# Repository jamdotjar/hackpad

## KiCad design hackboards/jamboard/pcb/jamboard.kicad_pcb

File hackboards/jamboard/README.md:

# Jamboard

BOM:
- 1x PCB
- 3d printed case
- 2x Orpheus Pico

https://chosfox.com/products/outemu-silent-honey-peach-switch?variant=44545283260610

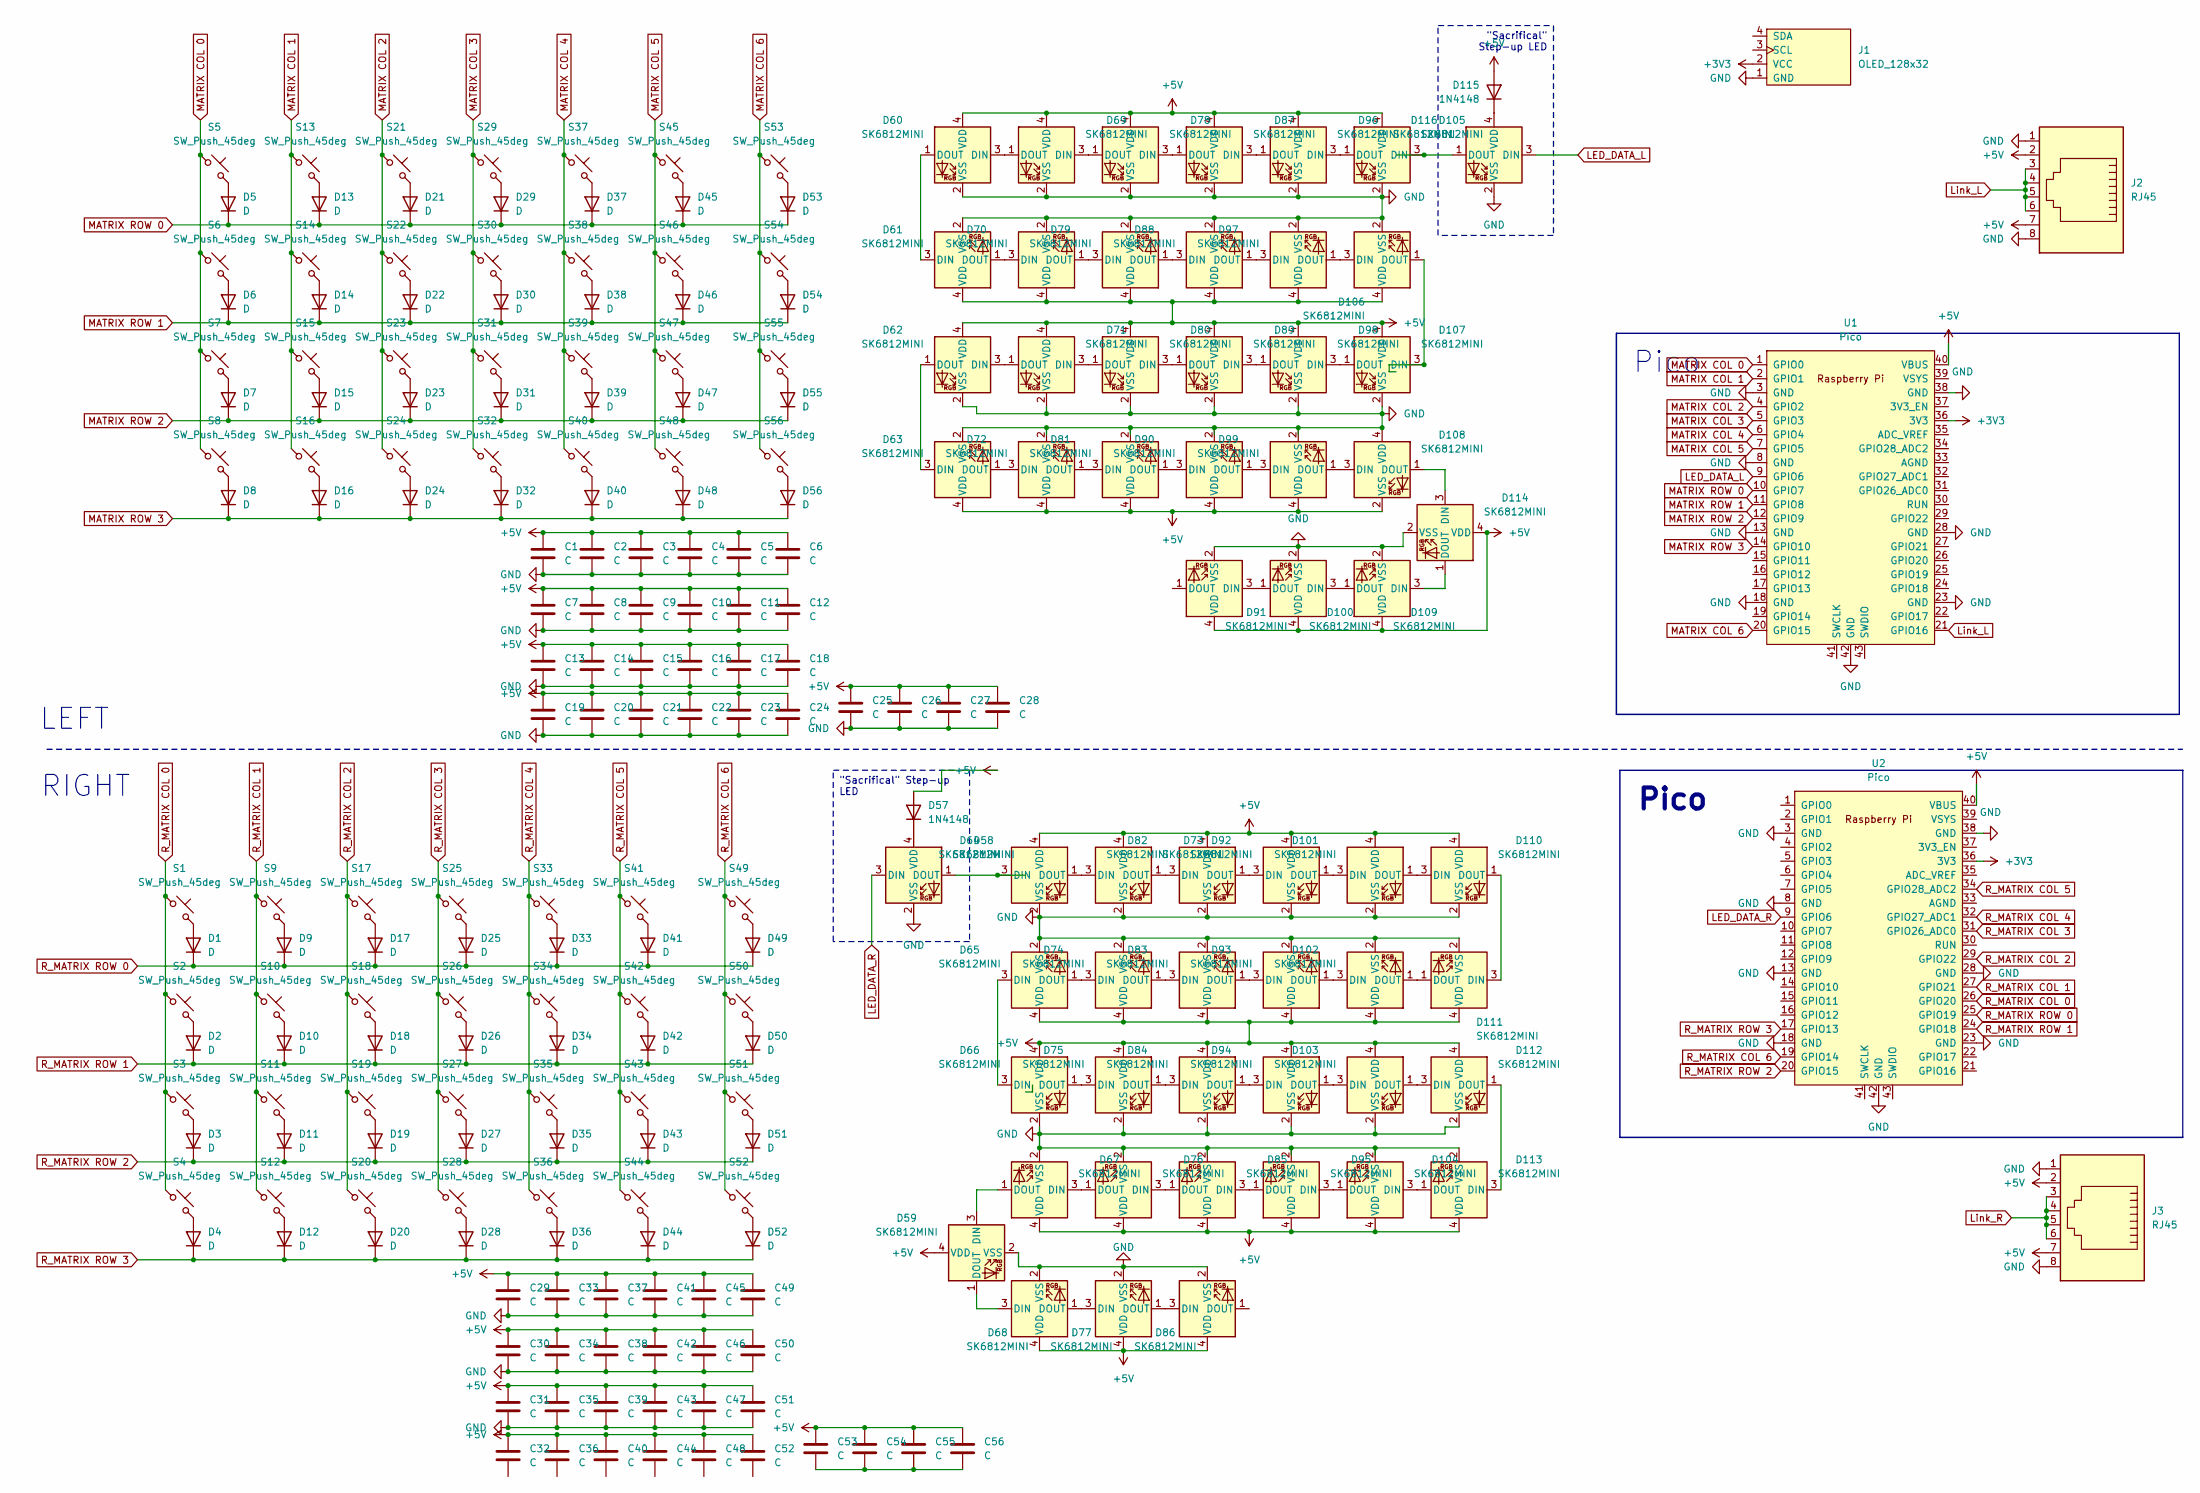
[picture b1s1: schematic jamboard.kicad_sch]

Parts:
C1, C2, C3, C4, C5, C6, C7, C8, C9, C10, C11, C12, C13, C14, C15, C16, C17, C18, C19, C20, C21, C22, C23, C24, C25, C26, C27, C28, C29, C30, C31, C32, C33, C34, C35, C36, C37, C38, C39, C40, C41, C42, C43, C44, C45, C46, C47, C48, C49, C50, C51, C52, C53, C54, C55, C56: C; C_0603_1608Metric_Pad1.08x0.95mm_HandSolder
D1, D2, D3, D4, D5, D6, D7, D8, D9, D10, D11, D12, D13, D14, D15, D16, D17, D18, D19, D20, D21, D22, D23, D24, D25, D26, D27, D28, D29, D30, D31, D32, D33, D34, D35, D36, D37, D38, D39, D40, D41, D42, D43, D44, D45, D46, D47, D48, D49, D50, D51, D52, D53, D54, D55, D56: D; Diode
D57, D115: 1N4148; D_DO-35_SOD27_P7.62mm_Horizontal
D58, D59, D60, D61, D62, D63, D64, D65, D66, D67, D68, D69, D70, D71, D72, D73, D74, D75, D76, D77, D78, D79, D80, D81, D82, D83, D84, D85, D86, D87, D88, D89, D90, D91, D92, D93, D94, D95, D96, D97, D98, D99, D100, D101, D102, D103, D104, D105, D106, D107, D108, D109, D110, D111, D112, D113, D114, D116: SK6812MINI; SK6812MINI-E
J1: OLED_128x32; SSD1306-0.91-OLED-4pin-128x32
J2, J3: RJ45; RJ45_Amphenol_54602-x08_Horizontal
S1, S2, S3, S4, S5, S6, S7, S8, S9, S10, S11, S12, S13, S14, S15, S16, S17, S18, S19, S20, S21, S22, S23, S24, S25, S26, S27, S28, S29, S30, S31, S32, S33, S34, S35, S36, S37, S38, S39, S40, S41, S42, S43, S44, S45, S46, S47, S48, S49, S50, S51, S52, S53, S54, S55, S56: SW_Push_45deg; MX-Hotswap-1U
U1, U2: Pico; RaspberryPi_Pico_Common

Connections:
+3V3: J1.2 (VCC), U1.36 (3V3), U2.36 (3V3)
+5V: C1.1, C2.1, C3.1, C4.1, C5.1, C6.1, C7.1, C8.1, C9.1, C10.1, C11.1, C12.1, C13.1, C14.1, C15.1, C16.1, C17.1, C18.1, C19.1, C20.1, C21.1, C22.1, C23.1, C24.1, C25.1, C26.1, C27.1, C28.1, C29.1, C30.1, C31.1, C32.1, C33.1, C34.1, C35.1, C36.1, C37.1, C38.1, C39.1, C40.1, C41.1, C42.1, C43.1, C44.1, C45.1, C46.1, C47.1, C48.1, C49.1, C50.1, C51.1, C52.1, C53.1, C54.1, C55.1, C56.1, D57.2 (A), D59.4 (VDD), D60.4 (VDD), D61.4 (VDD), D62.4 (VDD), D63.4 (VDD), D64.4 (VDD), D65.4 (VDD), D66.4 (VDD), D67.4 (VDD), D68.4 (VDD), D69.4 (VDD), D70.4 (VDD), D71.4 (VDD), D72.4 (VDD), D73.4 (VDD), D74.4 (VDD), D75.4 (VDD), D76.4 (VDD), D77.4 (VDD), D78.4 (VDD), D79.4 (VDD), D80.4 (VDD), D81.4 (VDD), D82.4 (VDD), D83.4 (VDD), D84.4 (VDD), D85.4 (VDD), D86.4 (VDD), D87.4 (VDD), D88.4 (VDD), D89.4 (VDD), D90.4 (VDD), D91.4 (VDD), D92.4 (VDD), D93.4 (VDD), D94.4 (VDD), D95.4 (VDD), D96.4 (VDD), D97.4 (VDD), D98.4 (VDD), D99.4 (VDD), D100.4 (VDD), D101.4 (VDD), D102.4 (VDD), D103.4 (VDD), D104.4 (VDD), D105.4 (VDD), D106.4 (VDD), D107.4 (VDD), D108.2 (VSS), D109.4 (VDD), D110.4 (VDD), D111.4 (VDD), D112.4 (VDD), D113.4 (VDD), D114.4 (VDD), D115.2 (A), J2.2, J2.7, J3.2, J3.7, U1.40 (VBUS), U2.40 (VBUS)
GND: C1.2, C2.2, C3.2, C4.2, C5.2, C6.2, C7.2, C8.2, C9.2, C10.2, C11.2, C12.2, C13.2, C14.2, C15.2, C16.2, C17.2, C18.2, C19.2, C20.2, C21.2, C22.2, C23.2, C24.2, C25.2, C26.2, C27.2, C28.2, C29.2, C30.2, C31.2, C33.2, C34.2, C35.2, C37.2, C38.2, C39.2, C41.2, C42.2, C43.2, C45.2, C46.2, C47.2, C49.2, C50.2, C51.2, D58.2 (VSS), D59.2 (VSS), D60.2 (VSS), D61.2 (VSS), D62.2 (VSS), D63.2 (VSS), D64.2 (VSS), D65.2 (VSS), D66.2 (VSS), D67.2 (VSS), D68.2 (VSS), D69.2 (VSS), D70.2 (VSS), D71.2 (VSS), D72.2 (VSS), D73.2 (VSS), D74.2 (VSS), D75.2 (VSS), D76.2 (VSS), D77.2 (VSS), D78.2 (VSS), D79.2 (VSS), D80.2 (VSS), D81.2 (VSS), D82.2 (VSS), D83.2 (VSS), D84.2 (VSS), D85.2 (VSS), D86.2 (VSS), D87.2 (VSS), D88.2 (VSS), D89.2 (VSS), D90.2 (VSS), D91.2 (VSS), D92.2 (VSS), D93.2 (VSS), D94.2 (VSS), D95.2 (VSS), D96.2 (VSS), D97.2 (VSS), D98.2 (VSS), D99.2 (VSS), D100.2 (VSS), D101.2 (VSS), D102.2 (VSS), D103.2 (VSS), D104.2 (VSS), D105.2 (VSS), D106.2 (VSS), D107.2 (VSS), D108.4 (VDD), D109.2 (VSS), D110.2 (VSS), D111.2 (VSS), D112.2 (VSS), D113.2 (VSS), D114.2 (VSS), D116.2 (VSS), J1.1 (GND), J2.1, J2.8, J3.1, J3.8, U1.3 (GND), U1.8 (GND), U1.13 (GND), U1.18 (GND), U1.23 (GND), U1.28 (GND), U1.38 (GND), U1.42 (GND), U2.3 (GND), U2.8 (GND), U2.13 (GND), U2.18 (GND), U2.23 (GND), U2.28 (GND), U2.38 (GND), U2.42 (GND)
LED_DATA_L: D116.3 (DIN), U1.9 (GPIO6)
LED_DATA_R: D58.3 (DIN), U2.9 (GPIO6)
Link_L: J2.3, J2.4, J2.5, J2.6, U1.21 (GPIO16)
Link_R: J3.3, J3.4, J3.5, J3.6
MATRIX COL 0: S5.1, S6.1, S7.1, S8.1, U1.1 (GPIO0)
MATRIX COL 1: S13.1, S14.1, S15.1, S16.1, U1.2 (GPIO1)
MATRIX COL 2: S21.1, S22.1, S23.1, S24.1, U1.4 (GPIO2)
MATRIX COL 3: S29.1, S30.1, S31.1, S32.1, U1.5 (GPIO3)
MATRIX COL 4: S37.1, S38.1, S39.1, S40.1, U1.6 (GPIO4)
MATRIX COL 5: S45.1, S46.1, S47.1, S48.1, U1.7 (GPIO5)
MATRIX COL 6: S53.1, S54.1, S55.1, S56.1, U1.20 (GPIO15)
MATRIX ROW 0: D5.1 (K), D13.1 (K), D21.1 (K), D29.1 (K), D37.1 (K), D45.1 (K), D53.1 (K), U1.10 (GPIO7)
MATRIX ROW 1: D6.1 (K), D14.1 (K), D22.1 (K), D30.1 (K), D38.1 (K), D46.1 (K), D54.1 (K), U1.11 (GPIO8)
MATRIX ROW 2: D7.1 (K), D15.1 (K), D23.1 (K), D31.1 (K), D39.1 (K), D47.1 (K), D55.1 (K), U1.12 (GPIO9)
MATRIX ROW 3: D8.1 (K), D16.1 (K), D24.1 (K), D32.1 (K), D40.1 (K), D48.1 (K), D56.1 (K), U1.14 (GPIO10)
unnamed: C53.2, C54.2, C55.2, C56.2
unnamed: D1.2 (A), S1.2
unnamed: D2.2 (A), S2.2
unnamed: D3.2 (A), S3.2
unnamed: D4.2 (A), S4.2
unnamed: D5.2 (A), S5.2
unnamed: D6.2 (A), S6.2
unnamed: D7.2 (A), S7.2
unnamed: D8.2 (A), S8.2
unnamed: D9.2 (A), S9.2
unnamed: D10.2 (A), S10.2
unnamed: D11.2 (A), S11.2
unnamed: D12.2 (A), S12.2
unnamed: D13.2 (A), S13.2
unnamed: D14.2 (A), S14.2
unnamed: D15.2 (A), S15.2
unnamed: D16.2 (A), S16.2
unnamed: D17.2 (A), S17.2
unnamed: D18.2 (A), S18.2
unnamed: D19.2 (A), S19.2
unnamed: D20.2 (A), S20.2
unnamed: D21.2 (A), S21.2
unnamed: D22.2 (A), S22.2
unnamed: D23.2 (A), S23.2
unnamed: D24.2 (A), S24.2
unnamed: D25.2 (A), S25.2
unnamed: D26.2 (A), S26.2
unnamed: D27.2 (A), S27.2
unnamed: D28.2 (A), S28.2
unnamed: D29.2 (A), S29.2
unnamed: D30.2 (A), S30.2
unnamed: D31.2 (A), S31.2
unnamed: D32.2 (A), S32.2
unnamed: D33.2 (A), S33.2
unnamed: D34.2 (A), S34.2
unnamed: D35.2 (A), S35.2
unnamed: D36.2 (A), S36.2
unnamed: D37.2 (A), S37.2
unnamed: D38.2 (A), S38.2
unnamed: D39.2 (A), S39.2
unnamed: D40.2 (A), S40.2
unnamed: D41.2 (A), S41.2
unnamed: D42.2 (A), S42.2
unnamed: D43.2 (A), S43.2
unnamed: D44.2 (A), S44.2
unnamed: D45.2 (A), S45.2
unnamed: D46.2 (A), S46.2
unnamed: D47.2 (A), S47.2
unnamed: D48.2 (A), S48.2
unnamed: D49.2 (A), S49.2
unnamed: D50.2 (A), S50.2
unnamed: D51.2 (A), S51.2
unnamed: D52.2 (A), S52.2
unnamed: D53.2 (A), S53.2
unnamed: D54.2 (A), S54.2
unnamed: D55.2 (A), S55.2
unnamed: D56.2 (A), S56.2
unnamed: D57.1 (K), D58.4 (VDD)
unnamed: D58.1 (DOUT), D64.3 (DIN)
unnamed: D59.3 (DIN), D67.1 (DOUT)
unnamed: D59.1 (DOUT), D68.3 (DIN)
unnamed: D60.3 (DIN), D69.1 (DOUT)
unnamed: D60.1 (DOUT), D61.3 (DIN)
unnamed: D61.1 (DOUT), D70.3 (DIN)
unnamed: D62.3 (DIN), D71.1 (DOUT)
unnamed: D62.1 (DOUT), D63.3 (DIN)
unnamed: D63.1 (DOUT), D72.3 (DIN)
unnamed: D64.1 (DOUT), D73.3 (DIN)
unnamed: D65.3 (DIN), D66.3 (DIN)
unnamed: D65.1 (DOUT), D74.3 (DIN)
unnamed: D66.1 (DOUT), D75.3 (DIN)
unnamed: D67.3 (DIN), D76.1 (DOUT)
unnamed: D68.1 (DOUT), D77.3 (DIN)
unnamed: D69.3 (DIN), D78.1 (DOUT)
unnamed: D70.1 (DOUT), D79.3 (DIN)
unnamed: D71.3 (DIN), D80.1 (DOUT)
unnamed: D72.1 (DOUT), D81.3 (DIN)
unnamed: D73.1 (DOUT), D82.3 (DIN)
unnamed: D74.1 (DOUT), D83.3 (DIN)
unnamed: D75.1 (DOUT), D84.3 (DIN)
unnamed: D76.3 (DIN), D85.1 (DOUT)
unnamed: D77.1 (DOUT), D86.3 (DIN)
unnamed: D78.3 (DIN), D87.1 (DOUT)
unnamed: D79.1 (DOUT), D88.3 (DIN)
unnamed: D80.3 (DIN), D89.1 (DOUT)
unnamed: D81.1 (DOUT), D90.3 (DIN)
unnamed: D82.1 (DOUT), D92.3 (DIN)
unnamed: D83.1 (DOUT), D93.3 (DIN)
unnamed: D84.1 (DOUT), D94.3 (DIN)
unnamed: D85.3 (DIN), D95.1 (DOUT)
unnamed: D87.3 (DIN), D96.1 (DOUT)
unnamed: D88.1 (DOUT), D97.3 (DIN)
unnamed: D89.3 (DIN), D98.1 (DOUT)
unnamed: D90.1 (DOUT), D99.3 (DIN)
unnamed: D100.3 (DIN), D109.1 (DOUT)
unnamed: D91.3 (DIN), D100.1 (DOUT)
unnamed: D92.1 (DOUT), D101.3 (DIN)
unnamed: D101.1 (DOUT), D110.3 (DIN)
unnamed: D93.1 (DOUT), D102.3 (DIN)
unnamed: D102.1 (DOUT), D111.1 (DOUT)
unnamed: D94.1 (DOUT), D103.3 (DIN)
unnamed: D103.1 (DOUT), D112.3 (DIN)
unnamed: D104.3 (DIN), D113.1 (DOUT)
unnamed: D95.3 (DIN), D104.1 (DOUT)
unnamed: D105.3 (DIN), D116.1 (DOUT)
unnamed: D96.3 (DIN), D105.1 (DOUT)
unnamed: D97.1 (DOUT), D106.3 (DIN)
unnamed: D106.1 (DOUT), D107.3 (DIN)
unnamed: D98.3 (DIN), D107.1 (DOUT)
unnamed: D99.1 (DOUT), D108.3 (DIN)
unnamed: D108.1 (DOUT), D114.3 (DIN)
unnamed: D109.3 (DIN), D114.1 (DOUT)
unnamed: D110.1 (DOUT), D111.3 (DIN)
unnamed: D112.1 (DOUT), D113.3 (DIN)
unnamed: D115.1 (K), D116.4 (VDD)
R_MATRIX COL 0: S1.1, S2.1, S3.1, S4.1, U2.26 (GPIO20)
R_MATRIX COL 1: S9.1, S10.1, S11.1, S12.1, U2.27 (GPIO21)
R_MATRIX COL 2: S17.1, S18.1, S19.1, S20.1, U2.29 (GPIO22)
R_MATRIX COL 3: S25.1, S26.1, S27.1, S28.1, U2.31 (GPIO26_ADC0)
R_MATRIX COL 4: S33.1, S34.1, S35.1, S36.1, U2.32 (GPIO27_ADC1)
R_MATRIX COL 5: S41.1, S42.1, S43.1, S44.1, U2.34 (GPIO28_ADC2)
R_MATRIX COL 6: S49.1, S50.1, S51.1, S52.1, U2.19 (GPIO14)
R_MATRIX ROW 0: D1.1 (K), D9.1 (K), D17.1 (K), D25.1 (K), D33.1 (K), D41.1 (K), D49.1 (K), U2.25 (GPIO19)
R_MATRIX ROW 1: D2.1 (K), D10.1 (K), D18.1 (K), D26.1 (K), D34.1 (K), D42.1 (K), D50.1 (K), U2.24 (GPIO18)
R_MATRIX ROW 2: D3.1 (K), D11.1 (K), D19.1 (K), D27.1 (K), D35.1 (K), D43.1 (K), D51.1 (K), U2.20 (GPIO15)
R_MATRIX ROW 3: D4.1 (K), D12.1 (K), D20.1 (K), D28.1 (K), D36.1 (K), D44.1 (K), D52.1 (K), U2.17 (GPIO13)

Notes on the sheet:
"Sacrifical" Step-up LED
Pico
RIGHT
LEFT

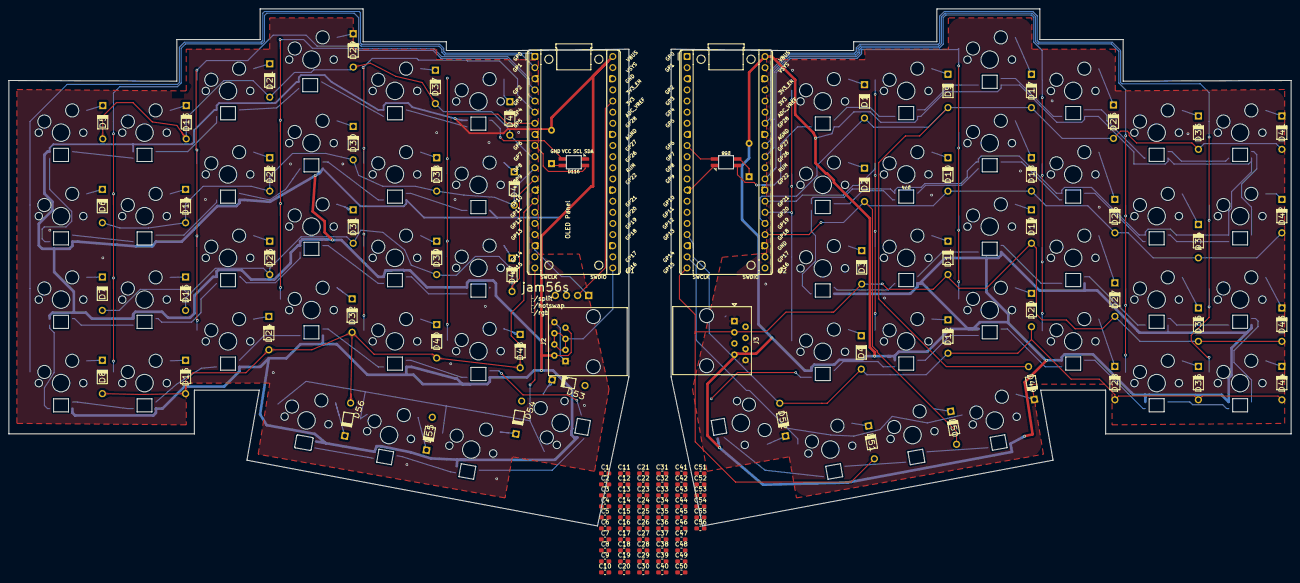
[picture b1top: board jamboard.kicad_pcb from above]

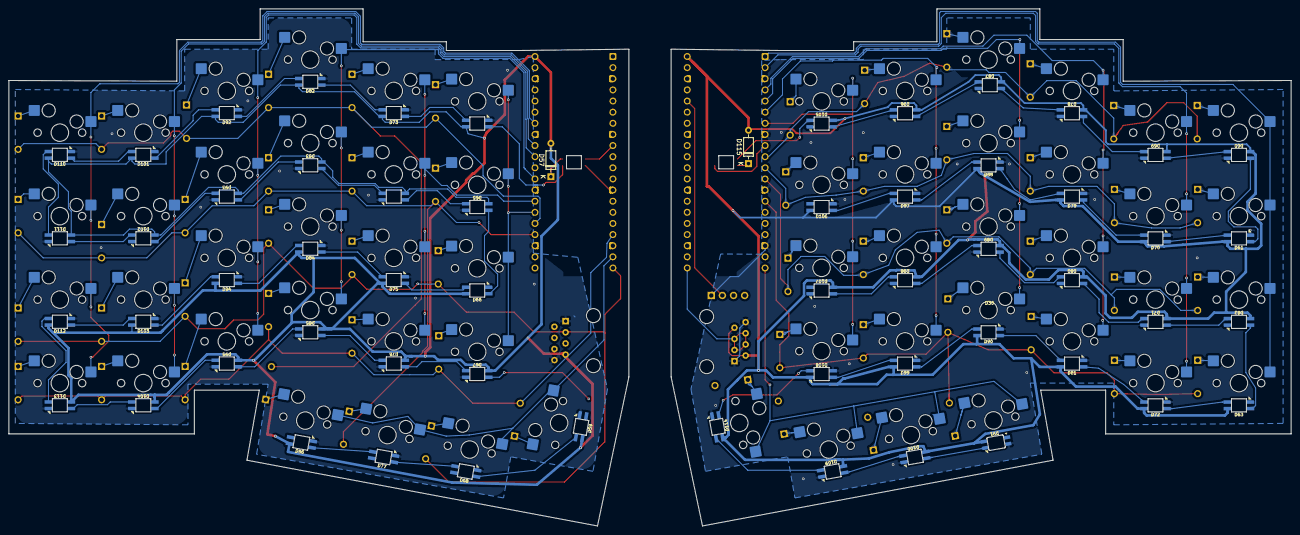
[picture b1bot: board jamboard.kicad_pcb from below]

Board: 2 copper layers, 292.6 x 118.0 mm, 233 parts (114 on the bottom side), 144 nets.

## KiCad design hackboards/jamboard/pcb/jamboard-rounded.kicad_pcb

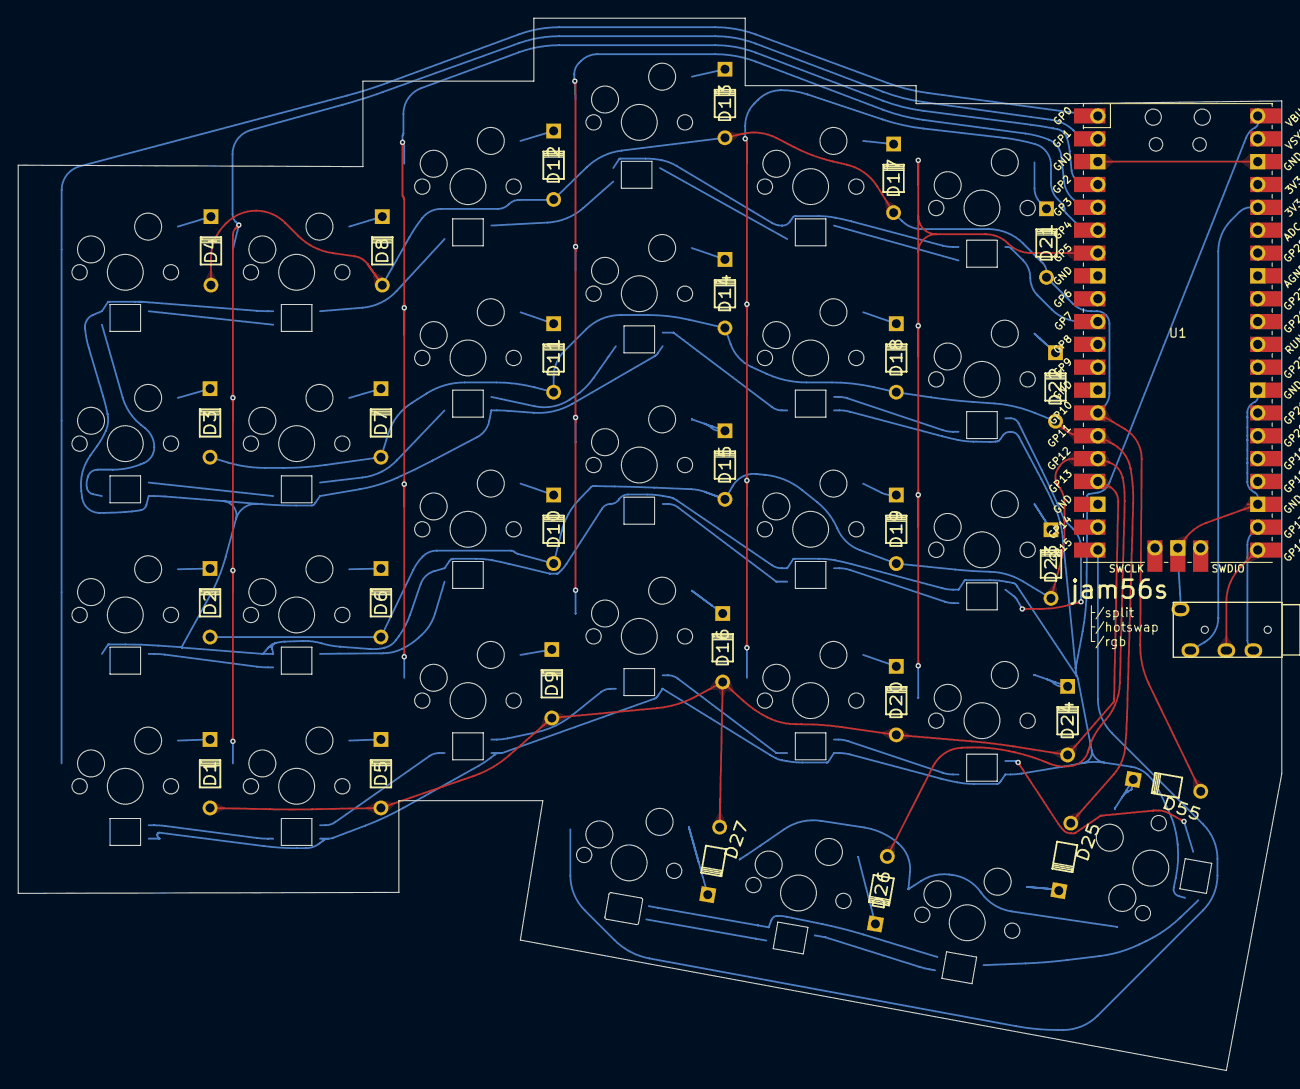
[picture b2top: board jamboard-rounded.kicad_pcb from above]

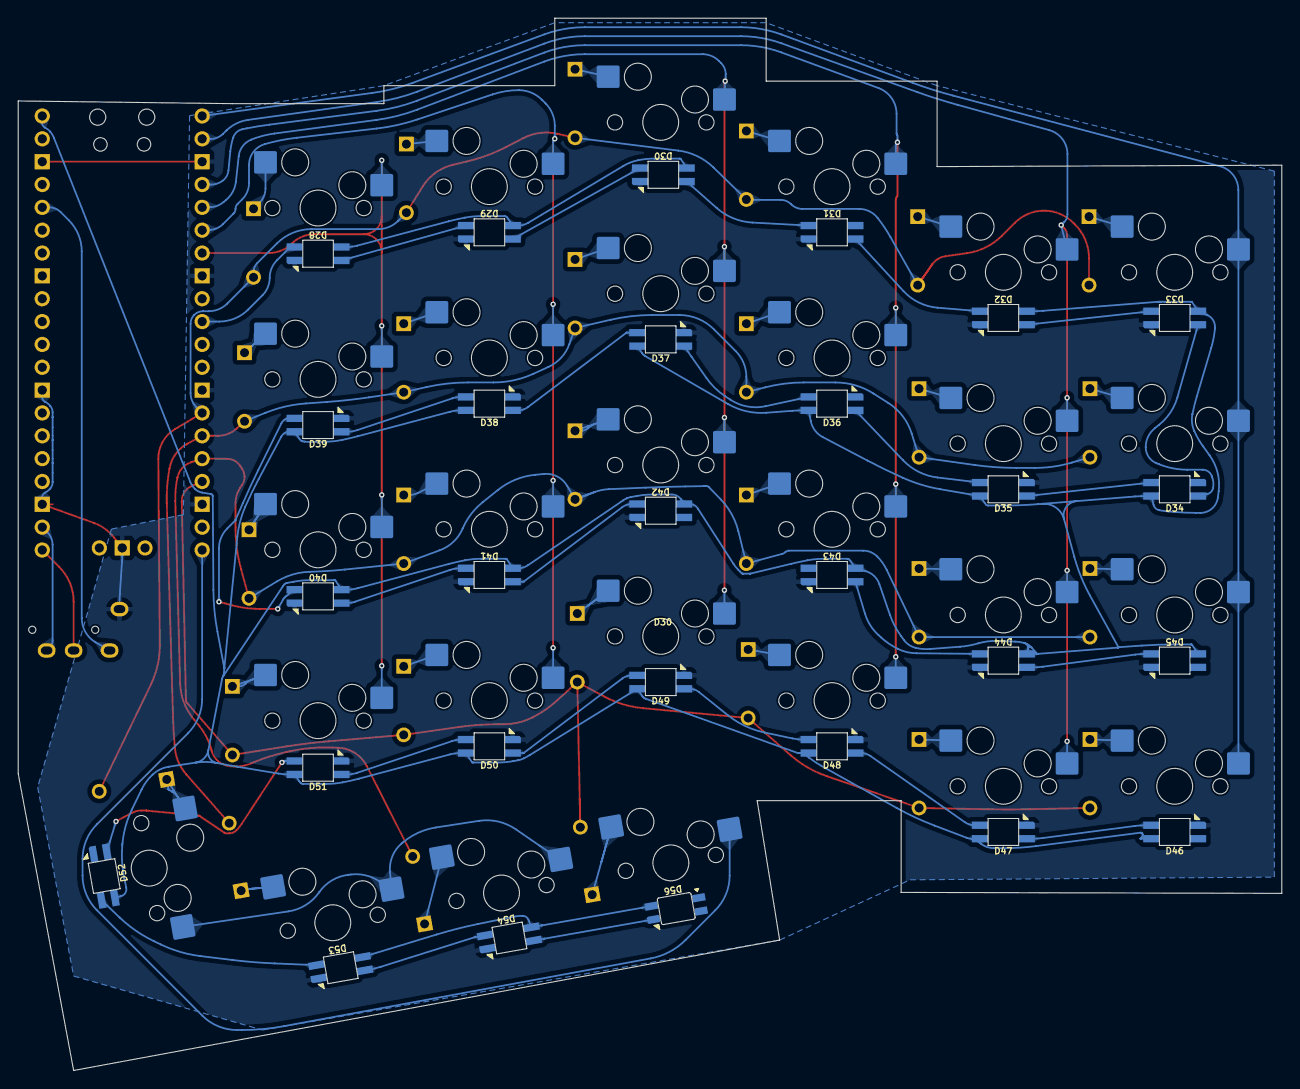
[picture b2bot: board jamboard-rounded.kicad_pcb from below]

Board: 2 copper layers, 140.5 x 117.0 mm, 86 parts (56 on the bottom side), 72 nets.

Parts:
D1, D2, D3, D4, D5, D6, D7, D8, D9, D10, D11, D12, D13, D14, D15, D16, D17, D18, D19, D20, D21, D22, D23, D24, D25, D26, D27, D55: D; Diode
D28, D29, D30, D31, D32, D33, D34, D35, D36, D37, D38, D39, D40, D41, D42, D43, D44, D45, D46, D47, D48, D49, D50, D51, D52, D53, D54: SK6812MINI; SK6812MINI-E
D56: SK6812MINI; SK6812-MINI-E
S1, S2, S3, S4, S5, S6, S7, S8, S9, S10, S11, S12, S13, S14, S15, S16, S17, S18, S19, S20, S21, S22, S23, S24, S25, S26, S27, S28: SW_Push_45deg; MX-Hotswap-1U
U1: Pico; RPi_Pico_SMD_TH
U2: TRRS; TRRS-PJ-320A

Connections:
+3V3: U1.36 (3V3), U2.2 (TIP)
+5V: D28.4 (VDD), D29.4 (VDD), D30.4 (VDD), D31.4 (VDD), D32.4 (VDD), D33.4 (VDD), D34.4 (VDD), D35.4 (VDD), D36.4 (VDD), D37.4 (VDD), D38.4 (VDD), D39.4 (VDD), D40.4 (VDD), D41.4 (VDD), D42.4 (VDD), D43.4 (VDD), D44.4 (VDD), D45.4 (VDD), D46.4 (VDD), D47.4 (VDD), D48.4 (VDD), D49.4 (VDD), D50.4 (VDD), D51.4 (VDD), D52.4 (VDD), D53.4 (VDD), D54.4 (VDD), D56.4 (VDD), U1.40 (VBUS)
GND: D28.2 (VSS), D29.2 (VSS), D30.2 (VSS), D31.2 (VSS), D32.2 (VSS), D33.2 (VSS), D34.2 (VSS), D35.2 (VSS), D36.2 (VSS), D37.2 (VSS), D38.2 (VSS), D39.2 (VSS), D40.2 (VSS), D41.2 (VSS), D42.2 (VSS), D43.2 (VSS), D44.2 (VSS), D45.2 (VSS), D46.2 (VSS), D47.2 (VSS), D48.2 (VSS), D49.2 (VSS), D50.2 (VSS), D51.2 (VSS), D52.2 (VSS), D53.2 (VSS), D54.2 (VSS), D56.2 (VSS), U1.3 (GND), U1.8 (GND), U1.13 (GND), U1.18 (GND), U1.23 (GND), U1.28 (GND), U1.38 (GND), U1.42 (GND), U2.1 (SLEEVE)
LED ROW 2: D33.1 (DOUT), D34.3 (DIN)
LED ROW 3: D40.1 (DOUT), D41.3 (DIN)
LED ROW 4: D47.1 (DOUT), D48.3 (DIN)
LED_ROW1: D28.3 (DIN), U1.10 (GPIO7)
MATRIX COL 0: S1.1, S2.1, S3.1, S4.1, U1.1 (GPIO0)
MATRIX COL 1: S5.1, S6.1, S7.1, S8.1, U1.2 (GPIO1)
MATRIX COL 2: S9.1, S10.1, S11.1, S12.1, U1.4 (GPIO2)
MATRIX COL 3: S13.1, S14.1, S15.1, S16.1, U1.5 (GPIO3)
MATRIX COL 4: S17.1, S18.1, S19.1, S20.1, U1.6 (GPIO4)
MATRIX COL 5: S21.1, S22.1, S23.1, S24.1, U1.7 (GPIO5)
MATRIX COL 6: S25.1, S26.1, S27.1, S28.1, U1.20 (GPIO15)
MATRIX ROW 0: D4.1 (K), D8.1 (K), D12.1 (K), D13.1 (K), D17.1 (K), D21.1 (K), D55.1 (K), U1.14 (GPIO10)
MATRIX ROW 1: D3.1 (K), D7.1 (K), D11.1 (K), D14.1 (K), D18.1 (K), D22.1 (K), D25.1 (K), U1.15 (GPIO11)
MATRIX ROW 2: D2.1 (K), D6.1 (K), D10.1 (K), D15.1 (K), D19.1 (K), D23.1 (K), D26.1 (K), U1.16 (GPIO12)
MATRIX ROW 3: D1.1 (K), D5.1 (K), D9.1 (K), D16.1 (K), D20.1 (K), D24.1 (K), D27.1 (K), U1.17 (GPIO13)
unnamed: D1.2 (A), S1.2
unnamed: D2.2 (A), S2.2
unnamed: D3.2 (A), S3.2
unnamed: D4.2 (A), S4.2
unnamed: D5.2 (A), S5.2
unnamed: D6.2 (A), S6.2
unnamed: D7.2 (A), S7.2
unnamed: D8.2 (A), S8.2
unnamed: D9.2 (A), S9.2
unnamed: D10.2 (A), S10.2
unnamed: D11.2 (A), S11.2
unnamed: D12.2 (A), S12.2
unnamed: D13.2 (A), S16.2
unnamed: D14.2 (A), S15.2
unnamed: D15.2 (A), S14.2
unnamed: D16.2 (A), S13.2
unnamed: D17.2 (A), S20.2
unnamed: D18.2 (A), S19.2
unnamed: D19.2 (A), S18.2
unnamed: D20.2 (A), S17.2
unnamed: D21.2 (A), S24.2
unnamed: D22.2 (A), S23.2
unnamed: D23.2 (A), S22.2
unnamed: D24.2 (A), S21.2
unnamed: D25.2 (A), S27.2
unnamed: D26.2 (A), S26.2
unnamed: D27.2 (A), S25.2
unnamed: D28.1 (DOUT), D29.3 (DIN)
unnamed: D29.1 (DOUT), D30.3 (DIN)
unnamed: D30.1 (DOUT), D31.3 (DIN)
unnamed: D31.1 (DOUT), D32.3 (DIN)
unnamed: D32.1 (DOUT), D33.3 (DIN)
unnamed: D34.1 (DOUT), D35.3 (DIN)
unnamed: D35.1 (DOUT), D36.3 (DIN)
unnamed: D36.1 (DOUT), D37.3 (DIN)
unnamed: D37.1 (DOUT), D38.3 (DIN)
unnamed: D38.1 (DOUT), D39.3 (DIN)
unnamed: D39.1 (DOUT), D40.3 (DIN)
unnamed: D41.1 (DOUT), D42.3 (DIN)
unnamed: D42.1 (DOUT), D43.3 (DIN)
unnamed: D43.1 (DOUT), D44.3 (DIN)
unnamed: D44.1 (DOUT), D45.3 (DIN)
unnamed: D45.1 (DOUT), D46.3 (DIN)
unnamed: D46.1 (DOUT), D47.3 (DIN)
unnamed: D48.1 (DOUT), D49.3 (DIN)
unnamed: D49.1 (DOUT), D50.3 (DIN)
unnamed: D50.1 (DOUT), D51.3 (DIN)
unnamed: D51.1 (DOUT), D52.3 (DIN)
unnamed: D52.1 (DOUT), D53.3 (DIN)
unnamed: D53.1 (DOUT), D54.3 (DIN)
unnamed: D54.1 (DOUT), D56.3 (DIN)
unnamed: D55.2 (A), S28.2
unnamed: U1.21 (GPIO16), U2.3 (RING1)
unnamed: U1.22 (GPIO17), U2.4 (RING2)

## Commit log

2025-03-19 jampad PCB stuff
